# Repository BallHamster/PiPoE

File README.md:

# PiPoE
Hello all! Welcome to my project, PiPoE.
## What it is
PiPoE is a custom made hat by me, that adds PoE functionality to the Rpi 4B SBC.
## How it works
This project uses a PoE manager board from the AG4500 family to supply power to the pi 4.
## How I made it

I had a little problem: There were no schematics or footprints for the pi 4 that contained the PoE pins. So I made them from the official measurements:

And also the module had no files as well, so I made them too using theese references:

# Final designs:
Schematic: 
PCB: 
3D: 
# BOM

| Ref no | Name | Desc | Pcs needed | Pcs minimum order | Price for needed/minimum ordered (USD) | Link |
|---|---|---|---|---|---|---|
| C2 | Rubycon 16YXJ470M8X11.5 (LCSC C432444) | 470uF 16V radial electrolytic, D8 x 11.5mm, 3.5mm pitch | 1 | 5 | 0.45 | [LCSC](https://www.lcsc.com/product-detail/C432444.html) |
| C3 | FH 0805B104K500NT (LCSC C38141) | 100nF 50V X7R 0805 ceramic | 1 | 100 | 0.68 | [LCSC](https://www.lcsc.com/product-detail/C38141.html) |
| C4 | HRE CGA0805X7R106K250MT (LCSC C6119932) | 10uF 25V X7R 0805 ceramic | 1 | 5 | 0.38 | [LCSC](https://www.lcsc.com/product-detail/C6119932.html) |
| D1-D8 | JSMSEMI SS210 (LCSC C20609197) | 100V 2A Schottky diode, SMA (DO-214AC) | 8 | 20 | 0.42 | [LCSC](https://www.lcsc.com/product-detail/C20609197.html) |
| D9 | JUXING SMAJ58A (LCSC C5182308) | 400W unidirectional TVS 58V standoff / 93.6V clamp, SMA | 1 | 10 | 0.15 | [LCSC](https://www.lcsc.com/product-detail/C5182308.html) |
| D10 | UBright red LED 0805 (LCSC C2295) | Red LED 0805, ~100mcd at 20mA | 1 | 50 | 0.54 | [LCSC](https://www.lcsc.com/product-detail/C2295.html) |
| R1 | Yageo RC1206FR-0727KL (LCSC C137340) | 27k 1% 0.25W thick film resistor, 1206 | 1 | 100 | 0.89 | [LCSC](https://www.lcsc.com/product-detail/C137340.html) |
| J1 | ZHOURI 2.54-2*20 | 2x20 (40-pin) female header socket, 2.54mm, straight, 8.5mm height - Pi GPIO | 1 | 5 | 1.54 | [LCSC](https://www.lcsc.com/product-detail/C2977589.html) |
| J2 | ZHOURI 2.54-2*2 | 2x2 (4-pin) female header socket, 2.54mm, straight, 8.5mm height - Pi PoE | 1 | 10 | 0.76 | [LCSC](https://www.lcsc.com/product-detail/C2977590.html) |
| AG1 | Silvertel AG5405 | PoE module | 1 | 1 | 16.00 | [Mouser](https://hu.mouser.com/en/ProductDetail/Silvertel/AG5405) |
| | | | | | **Total cost: 21.81** | |

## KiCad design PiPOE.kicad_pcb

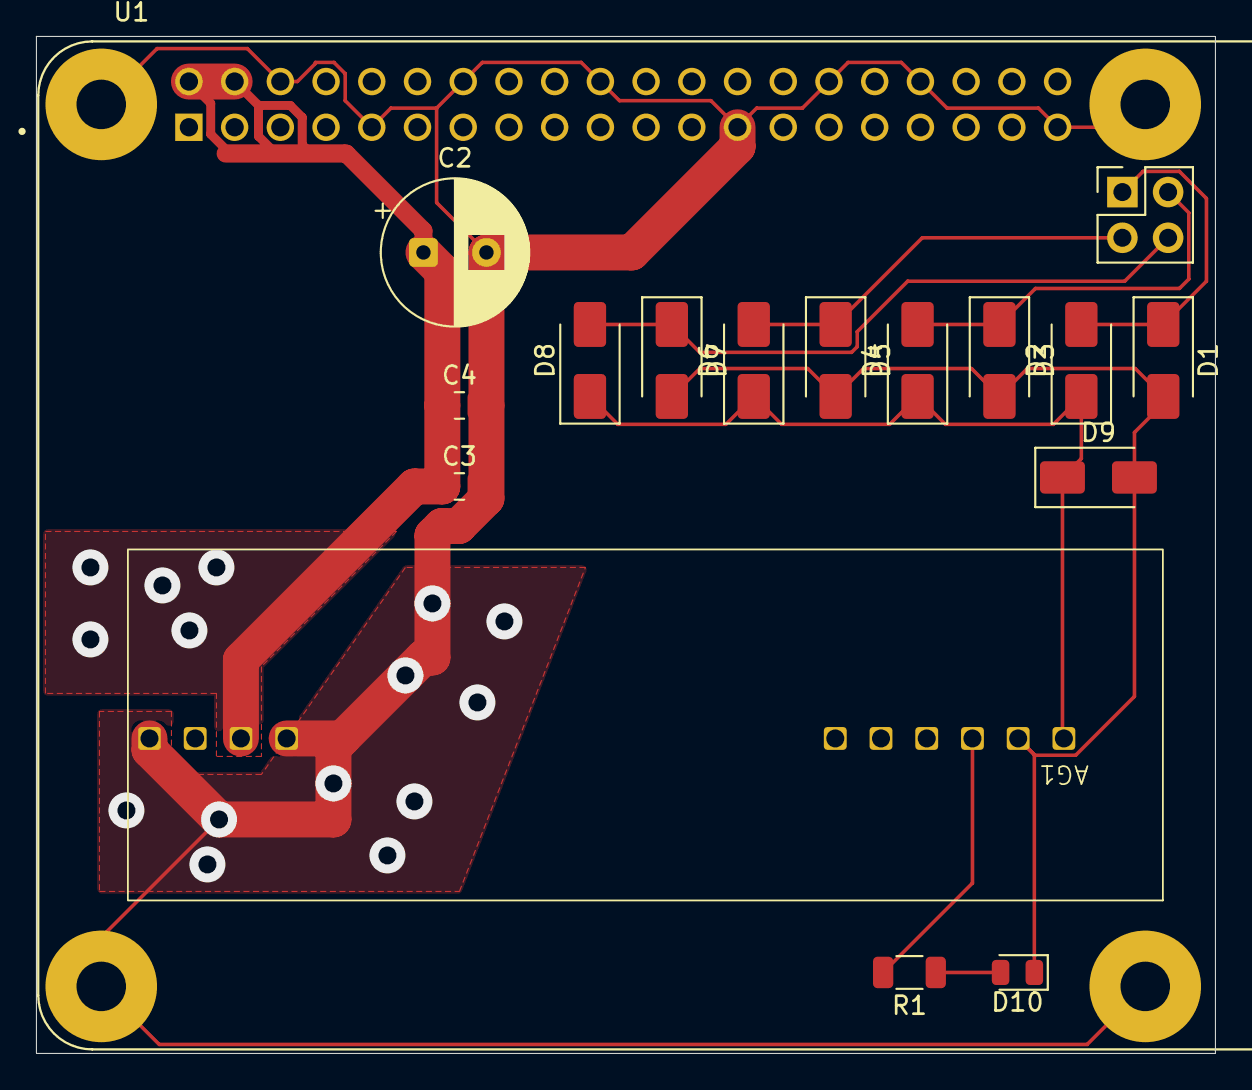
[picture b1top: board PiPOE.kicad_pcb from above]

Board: 2 copper layers, 65.5 x 56.5 mm, 16 parts (0 on the bottom side), 10 nets.

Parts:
AG1: Ag5400
C2: 470 uF; CP_Radial_D8.0mm_P3.50mm
C3: 100 nF; C_0805_2012Metric
C4: 10 uF; C_0805_2012Metric
D1, D2, D3, D4, D5, D6, D7, D8: SS210; D_SMA
D9: SMAJ58A; D_SMA
D10: LED; LED_0805_2012Metric
R1: 27 kOhm; R_1206_3216Metric
U1: Rpi_poe 4b; rpi_poe

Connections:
+5V: AG1.8 (+VDC), C2.1, C3.1, C4.1, U1.2 (5V0), U1.4 (5V0)
/Anode: AG1.2 (VIN-), D1.2 (A), D3.2 (A), D5.2 (A), D7.2 (A), D9.2 (A2), D10.1 (K)
/Cathode: AG1.1 (VIN+), D2.1 (K), D4.1 (K), D6.1 (K), D8.1 (K), D9.1 (A1)
GND: AG1.7 (-VDC), AG1.10 (-VDC), C2.2, C3.2, C4.2, U1.6 (GND), U1.9 (GND), U1.14 (GND), U1.20 (GND), U1.25 (GND), U1.30 (GND), U1.34 (GND), U1.39 (GND), U1.S1 (SHIELD), U1.S2 (SHIELD), U1.S3 (SHIELD), U1.S4 (SHIELD)
unnamed: AG1.3 (AT-DET), R1.2
unnamed: D1.1 (K), D2.2 (A), U1.51 (POE01/TR01)
unnamed: D3.1 (K), D4.2 (A), U1.52 (POE02/TR00)
unnamed: D5.1 (K), D6.2 (A), U1.53 (POE03/TR03)
unnamed: D7.1 (K), D8.2 (A), U1.54 (POE04/TR02)
unnamed: D10.2 (A), R1.1
